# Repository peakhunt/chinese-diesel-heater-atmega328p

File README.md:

# DANGEROUS
please don't use it if you don't know what you are doing.  
this is still a work in progress and I'm just using it  
as an emergency for my personal heating in my workshop  
so that I can have a warm winter at least.  
  
some documents will be posted here later for those brave souls interested in this.

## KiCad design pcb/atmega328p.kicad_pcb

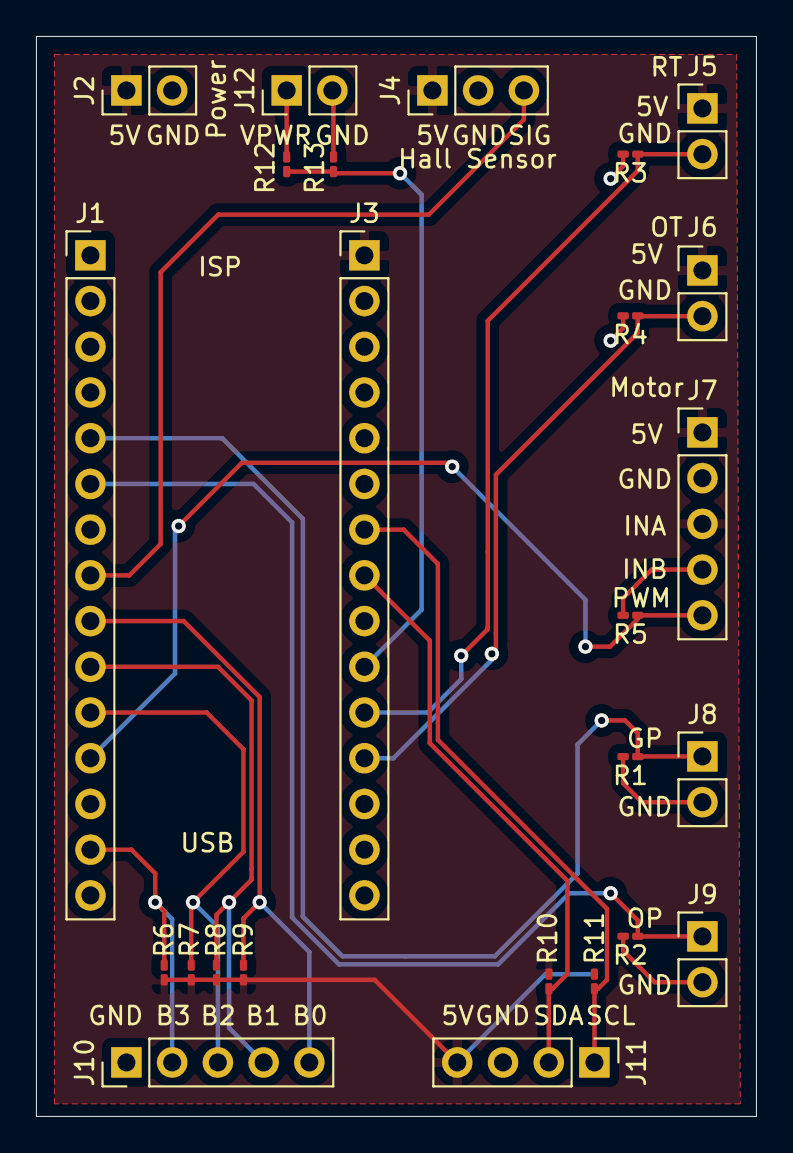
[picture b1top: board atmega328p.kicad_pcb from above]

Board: 2 copper layers, 40.0 x 60.0 mm, 25 parts (0 on the bottom side), 16 nets.

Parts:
J1: Arduini MINI Left; PinHeader_1x15_P2.54mm_Vertical
J2, J12: Power; PinHeader_1x02_P2.54mm_Vertical
J3: Arduini MINI Right; PinHeader_1x15_P2.54mm_Vertical
J4: Hall Sensor; PinHeader_1x03_P2.54mm_Vertical
J5: Room Temperature; PinHeader_1x02_P2.54mm_Vertical
J6: Outlet Temperature; PinHeader_1x02_P2.54mm_Vertical
J7: Motor; PinHeader_1x05_P2.54mm_Vertical
J8: Glow Plug; PinHeader_1x02_P2.54mm_Vertical
J9: Oil Pump; PinHeader_1x02_P2.54mm_Vertical
J10: Buttons; PinHeader_1x05_P2.54mm_Vertical
J11: I2C; PinHeader_1x04_P2.54mm_Vertical
R1, R2, R5, R6, R7, R8, R9: 2K; R_0201_0603Metric_Pad0.64x0.40mm_HandSolder
R3, R4: 51K; R_0201_0603Metric_Pad0.64x0.40mm_HandSolder
R10, R11: 1K; R_0201_0603Metric_Pad0.64x0.40mm_HandSolder
R12: 6.8K; R_0201_0603Metric_Pad0.64x0.40mm_HandSolder
R13: 3.3K; R_0201_0603Metric_Pad0.64x0.40mm_HandSolder

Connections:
/5V: J2.1, J3.1, J4.1, J5.1, J6.1, J7.1, J7.3, J11.4, R6.2, R7.2, R8.2, R9.2, R10.1, R11.1
/12V: J12.1, R12.1
/BTN0: J1.9, J10.5, R9.1
/BTN1: J1.10, J10.4, R8.1
/BTN2: J1.11, J10.3, R7.1
/BTN3: J1.14, J10.2, R6.1
/GP_SIG: J1.5, J8.1, R1.1
/HS_INPUT: J1.8, J4.3
/M_PWM: J1.12, J7.5, R5.1
/OP_SIG: J1.6, J9.1, R2.1
/OT: J3.12, J6.2, R4.1
/RT: J3.11, J5.2, R3.1
/SCL: J3.7, J11.1, R11.2
/SDA: J3.8, J11.2, R10.2
/VPWR: J3.10, R12.2, R13.1
GND: J2.2, J3.2, J4.2, J7.2, J7.4, J8.2, J9.2, J10.1, J11.3, J12.2, R1.2, R2.2, R3.2, R4.2, R5.2, R13.2

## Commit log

2020-11-30 doc update
2020-11-30 Create LICENSE
2020-11-30 disabling settings command for more memory
2020-11-30 adding .gitignore
2020-12-01 changed oil pump min/max frequency. this could burn the heater if fan is malfunctioning
2020-12-01 a bunch of string optimization macros to reduce sram usage. Soon I will move to stm32 for a new development
2020-12-01 another attempt to reduce sram usage
2020-12-01 commands to change settings
2020-12-01 a bunch of changes for the cold tonight
2020-12-07 adding ntc50k support for outlet temperature measurement. the result is highly inaccurate but it can be used for flame detection at least
2020-12-07 chaging default options to my optimal
2020-12-08 changed step settings
2020-12-08 changed ntc50 data gathering mechanism. now it is synchronized with adc. added a simple low pass filter
2020-12-08 added option not to use debouncer and switched to callback mechanism primarily to interface with hall sensor to detect if motor is running
2020-12-08 changed to ATOMIC_BLOCK with restore state in event_set
2020-12-08 added some comments about interrupt enable/disable not to forget
2020-12-08 added experimental motor running detection code
2020-12-11 new ntc50k calculation
2020-12-11 fixed a buf of not setting oil pump startup frequency when starting
2020-12-13 ntc50k bug fix
2021-02-15 adding pcb
2021-02-15 added batter power adc
2021-02-20 added ntc50k for room temperature
